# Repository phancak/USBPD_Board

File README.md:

# ⚡ Modular Power Distribution & USB-PD System

<div align="center">
  
  <br>
  <em>4-layer PCB diagram.</em>
</div>

### Intelligent Multi-Source Power Management for Mixed-Signal Platforms

## 📑 Quick Access
* [**📂 View Project Schematics (PDF)**](./Schematics/USBPD_Board_Schematics.pdf)

## 📖 Overview
This project is a high-efficiency, multi-input **Power Distribution Board** designed to provide stable, low-noise rails for interchangeable high-performance modules. It serves as the primary power hub for my **24-bit Precision ADC** and **STM32H7S3 System-on-Module** projects.

The system is engineered for maximum field flexibility, allowing a single instrumentation stack to be powered via laboratory bench supplies, USB-C PD sources, or mobile battery packs.

---

## 🛠 Technical Architecture

### 1. Power Entry & Negotiation
The board features a triple-redundant input strategy to support diverse operating environments:
* **USB Power Delivery:** Utilizes an **MCP2221A-I/ST** USB-to-I2C bridge to communicate with PD controllers and negotiate specific voltage profiles.
* **DC Input:** A standard barrel jack for **12V DC** wall converters, ideal for stationary bench-top development.
* **Battery Port:** A dedicated high-current connector for **Lithium-Ion/Polymer battery packs**, enabling untethered mobile data acquisition.

### 2. Digitally Enhanced Conversion
At the core is the **MCP19061-E/RTB**, a Digitally Enhanced Power Analog (DEPA) controller. 
* **Integrated MCU Control:** Combines the performance of an analog peak current mode controller with the flexibility of a microcontroller.
* **Dynamic Regulation:** Enables real-time telemetry and adjustment of output levels to match the requirements of the downstream load.
* **Protection Circuitry:** Hardware-level Under-Voltage Lockout (UVLO), Over-Voltage Protection (OVP), and thermal shutdown.

### 3. Distribution & Filtering
* **4-Way Power Bus:** Features four precision power connectors to distribute clean rails to a stack of interchangeable boards.
* **Noise Mitigation:** Designed with localized LC filtering and optimized PCB return paths to ensure switching noise from the DC-DC stage does not compromise the 120dB SNR performance of connected ADC modules.

---

## 📐 Hardware Specifications

| Feature | Component / Specification |
| :--- | :--- |
| **Main Controller** | Microchip MCP19061 (Integrated MCU + PWM) |
| **USB Interface** | MCP2221A-I/ST (USB-to-I2C/UART Bridge) |
| **Input Range** | Negotiated USB-PD / 12V DC / Battery |
| **Topology** | Synchronous Buck-Boost Converter |
| **Output Ports** | 4x Interconnect Headers |

---

## 🏗 System Integration Philosophy
This board was developed to solve the "Power Bottleneck" in modular hardware design. By decoupling the power stage from the logic and sensing stages, the system achieves:

1.  **High Modularity:** The "Interchangeable Device" architecture allows for swapping analog front-ends or digital processing units without redesigning the power delivery network.
2.  **Field Readiness:** The seamless transition to battery power makes the entire instrumentation stack viable for real-world environmental and oceanographic data collection.
3.  **Stability:** Centralized regulation reduces ground loops and phase coherency issues common in multi-board "nest" wiring.

---

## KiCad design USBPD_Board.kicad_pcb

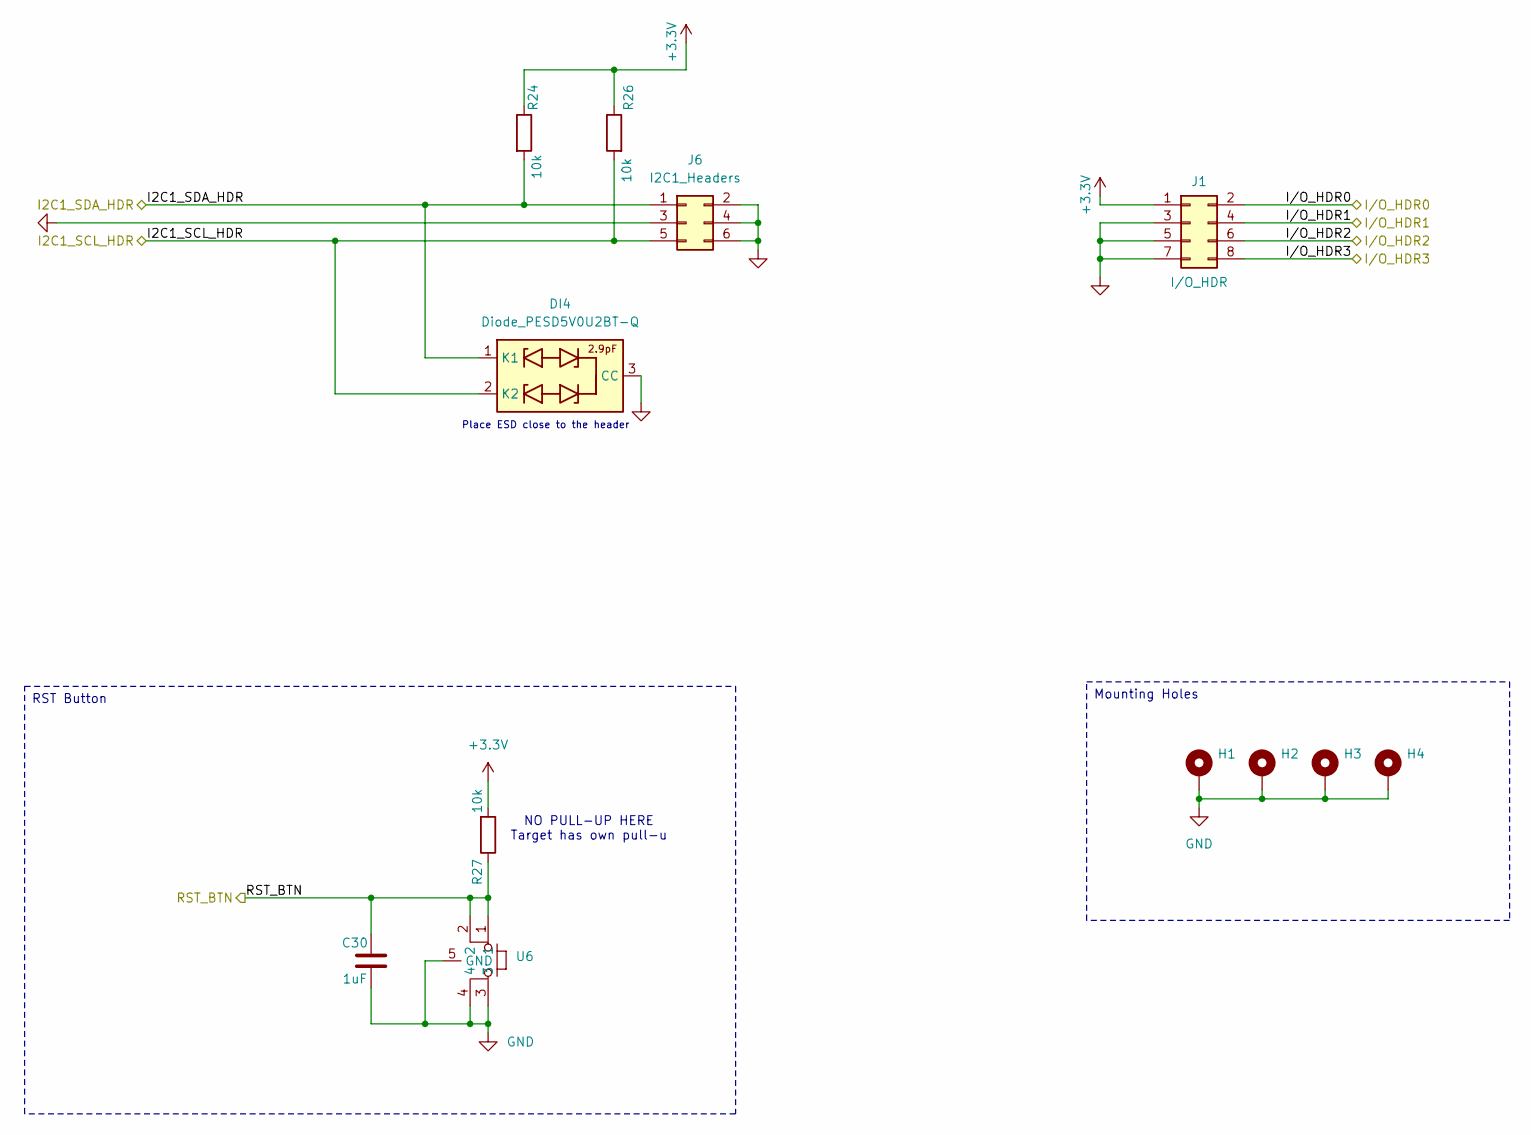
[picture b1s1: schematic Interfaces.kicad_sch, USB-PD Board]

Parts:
C30: 1uF; C_0805_2012Metric
DI4: Diode_PESD5V0U2BT-Q; SOT-23; Manufacturer_Part_Number BZX84C6V2-7-F; Mouser Part Number 621-BZX84C6V2-F
H1, H2, H3, H4: MountingHole_Pad; MountingHole_3.2mm_M3_Pad
J1: I/O_HDR; PinHeader_2x04_P2.54mm_Horizontal
J6: I2C1_Headers; PinHeader_2x03_P2.54mm_Horizontal
R24, R26, R27: 10k; R_0805_2012Metric
U6: Button_KMR231GLFS

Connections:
+3.3V: J1.1, R24.1, R26.1, R27.2; also elsewhere on the board
/Interfaces/I2C1_SCL_HDR: DI4.2 (K2), J6.5, R26.2; also elsewhere on the board
/Interfaces/I2C1_SDA_HDR: DI4.1 (K1), J6.1, R24.2; also elsewhere on the board
/Interfaces/I/O_HDR0: J1.2; also elsewhere on the board
/Interfaces/I/O_HDR1: J1.4; also elsewhere on the board
/Interfaces/I/O_HDR2: J1.6; also elsewhere on the board
/Interfaces/I/O_HDR3: J1.8; also elsewhere on the board
/Interfaces/RST_BTN: C30.2, R27.1, U6.1, U6.2; also elsewhere on the board
GND: C30.1, DI4.3 (CC), H1.1, H2.1, H3.1, H4.1, J1.3, J1.5, J1.7, J6.2, J6.3, J6.4, J6.6, U6.3, U6.4, U6.5 (GND); also elsewhere on the board

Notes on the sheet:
Place ESD close to the header
NO PULL-UP HERE Target has own pull-u
Mounting Holes
RST Button

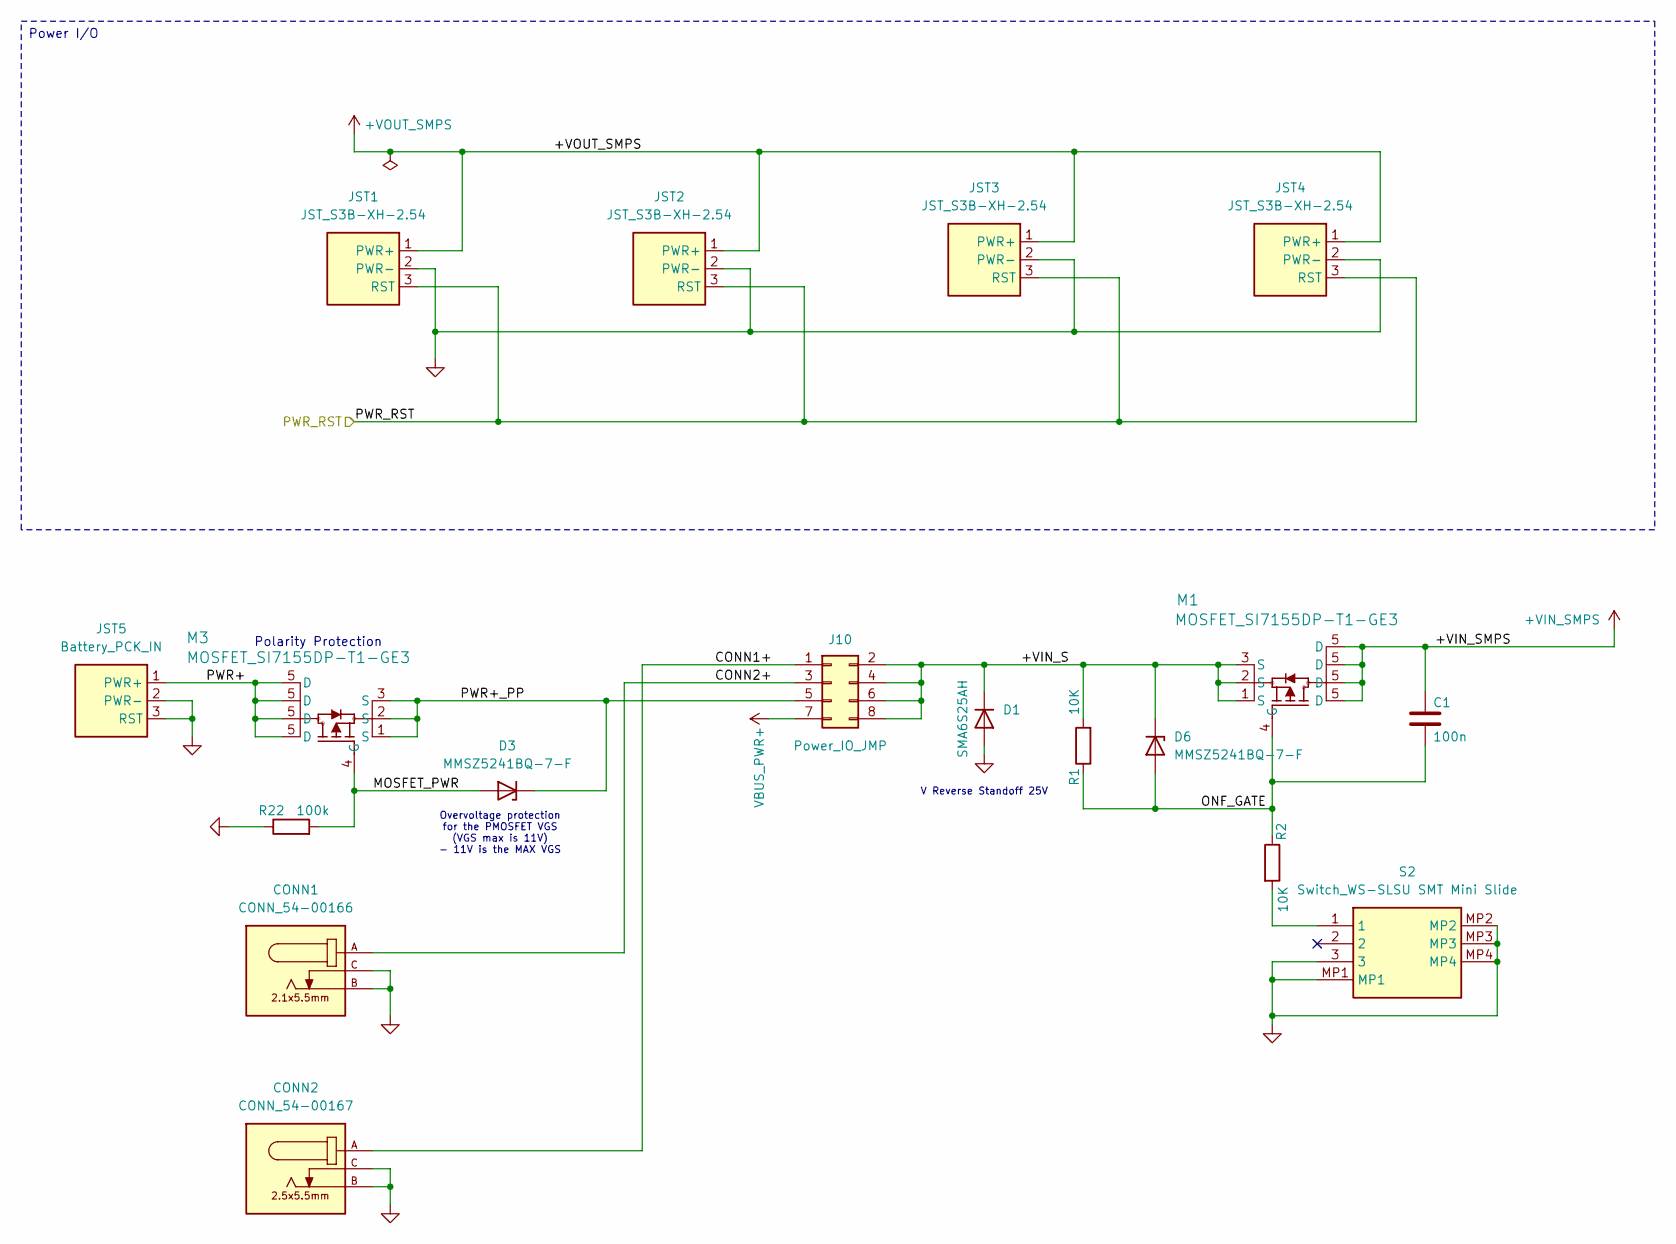
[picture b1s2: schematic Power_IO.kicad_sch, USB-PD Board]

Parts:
C1: 100n; C_0805_2012Metric
CONN1: CONN_54-00166; PARTREV A
CONN2: CONN_54-00167; PARTREV A
D1: SMA6S25AH; D_SOD-123
D3, D6: MMSZ5241BQ-7-F; D_SOD-123
J10: Power_IO_JMP; PinHeader_2x04_P2.54mm_Vertical
JST1, JST2, JST3, JST4: JST_S3B-XH-2.54; JST_S3B-XH-SHDRRA3W64P0X250_1X3_990X1150X610P; Mouser Part Number 306-S3BXHA1LFSN
JST5: Battery_PCK_IN; JST_S3B-XH-SHDRRA3W64P0X250_1X3_990X1150X610P; Mouser Part Number 306-S3BXHA1LFSN
M1, M3: MOSFET_SI7155DP-T1-GE3; MOSFET_SI7155DPT1GE3
R1, R2: 10K; R_0805_2012Metric
R22: 100k; R_0805_2012Metric
S2: Switch_WS-SLSU SMT Mini Slide; Mouser Part Number 710-450404015514

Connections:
+VIN_SMPS: C1.1, M1.5 (D); also elsewhere on the board
+VOUT_SMPS: JST1.1 (PWR+), JST2.1 (PWR+), JST3.1 (PWR+), JST4.1 (PWR+); also elsewhere on the board
/Interfaces/RST_BTN: JST1.3 (RST), JST2.3 (RST), JST3.3 (RST), JST4.3 (RST); also elsewhere on the board
/Power_IO/+VIN_S: D1.1 (K), D6.1 (K), J10.2, J10.4, J10.6, J10.8, M1.1 (S), M1.2 (S), M1.3 (S), R1.2
/Power_IO/CONN1+: CONN2.A, J10.1
/Power_IO/CONN2+: CONN1.A, J10.3
/Power_IO/MOSFET_PWR: D3.2 (A), M3.4 (G), R22.2
/Power_IO/ONF_GATE: C1.2, D6.2 (A), M1.4 (G), R1.1, R2.1
/Power_IO/PWR+: JST5.1 (PWR+), M3.5 (D)
/Power_IO/PWR+_PP: D3.1 (K), J10.5, M3.1 (S), M3.2 (S), M3.3 (S)
GND: CONN1.B, CONN1.C, CONN2.B, CONN2.C, D1.2 (A), JST1.2 (PWR-), JST2.2 (PWR-), JST3.2 (PWR-), JST4.2 (PWR-), JST5.2 (PWR-), JST5.3 (RST), R22.1, S2.3, S2.MP1, S2.MP2, S2.MP3, S2.MP4; also elsewhere on the board
unnamed: R2.2, S2.1
VBUS_PWR+: J10.7; also elsewhere on the board

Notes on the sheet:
Overvoltage protection for the PMOSFET VGS (VGS max is 11V) - 11V is the MAX VGS
V Reverse Standoff 25V
Polarity Protection
Power I/O

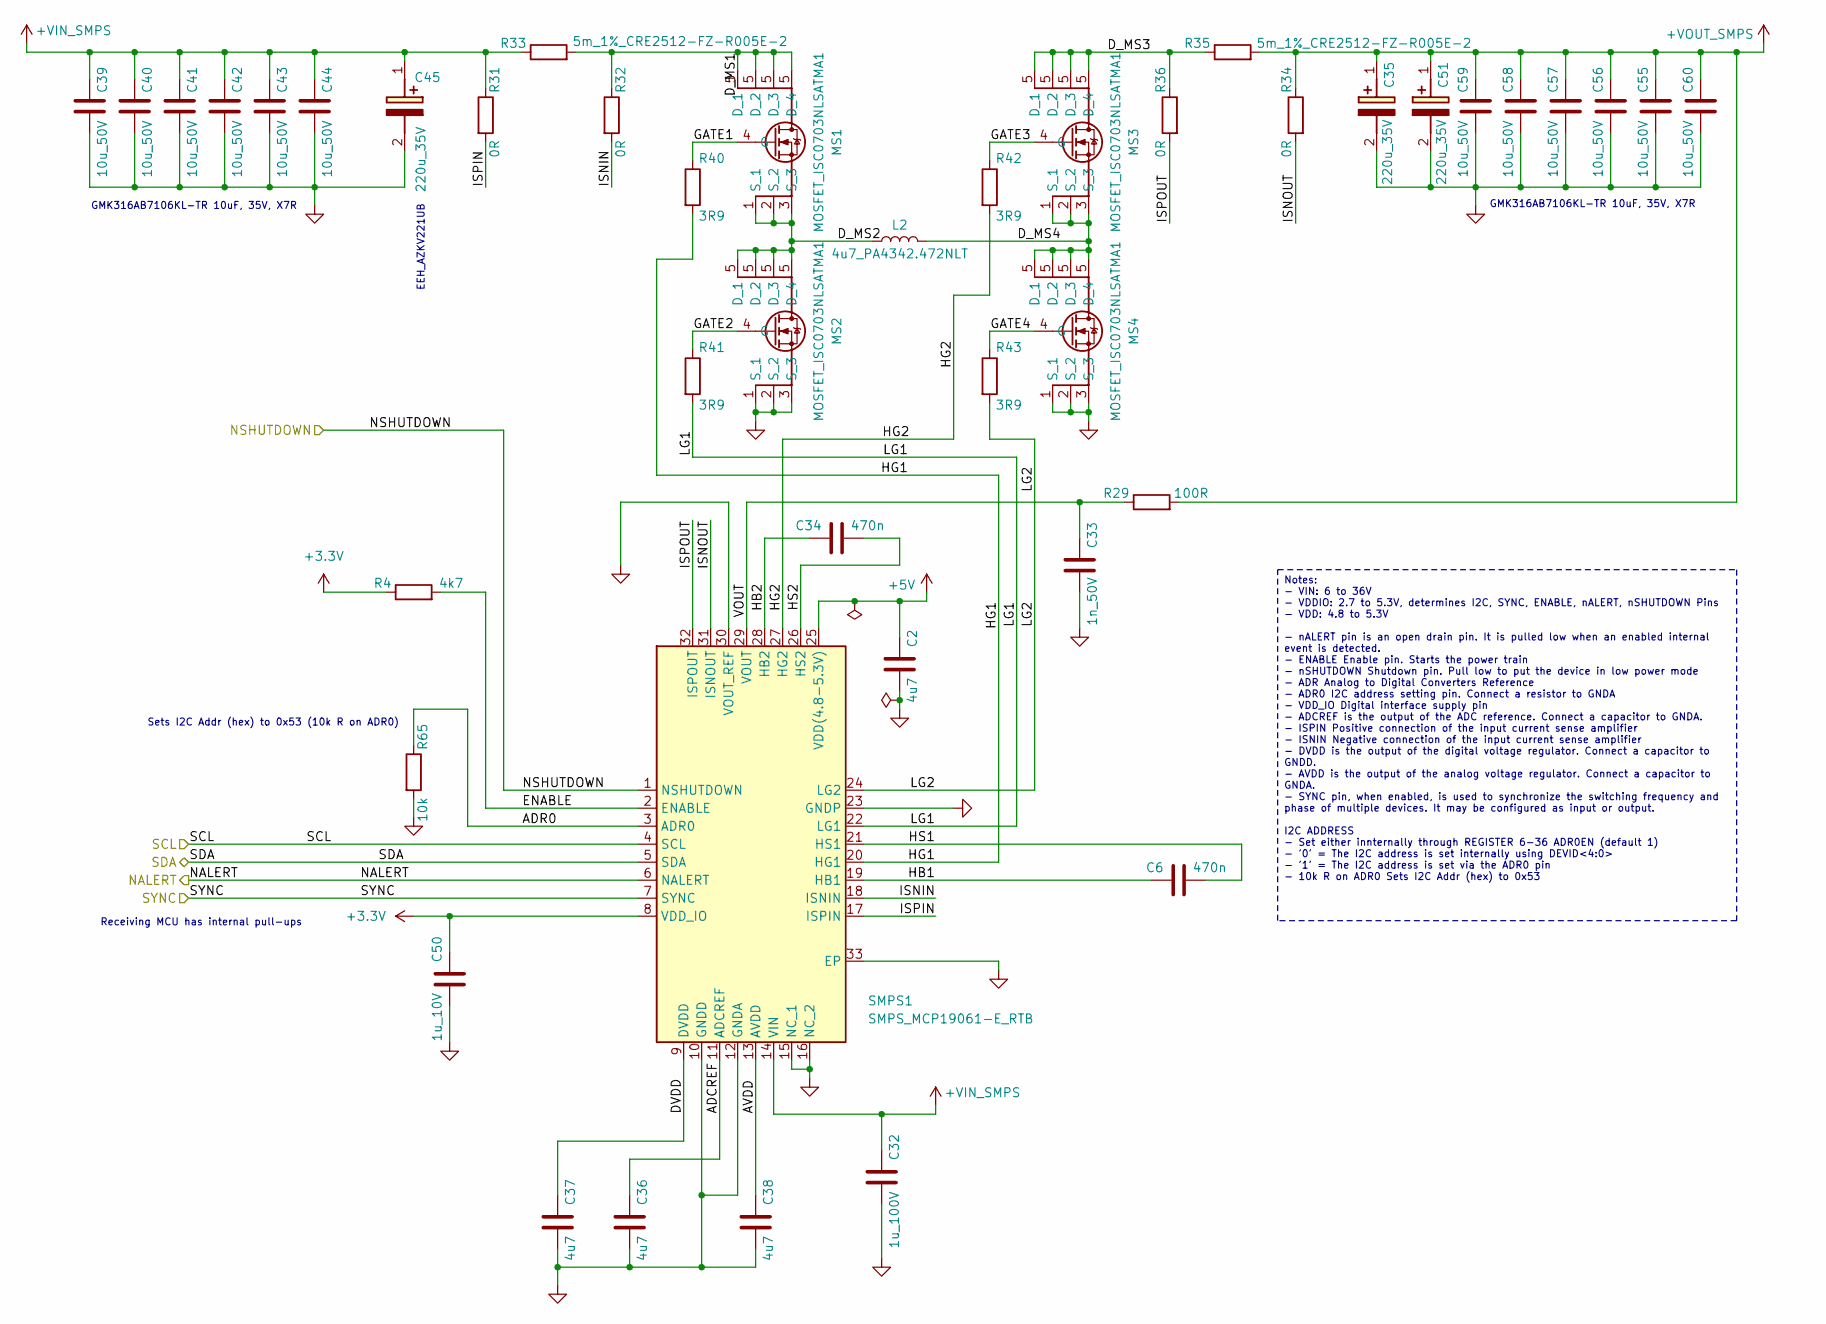
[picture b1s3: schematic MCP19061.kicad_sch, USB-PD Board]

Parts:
C2, C36, C37, C38: 4u7; C_0805_2012Metric
C6, C34: 470n; C_0805_2012Metric
C32: 1u_100V; C_0805_2012Metric
C33: 1n_50V; C_0805_2012Metric
C35, C45, C51: 220u_35V; C_EEHAZKV221UB_CAPPRD350W60D800H950; Mouser Part Number 80-T530Y337M6ATE6
C39, C40, C41, C42, C43, C44, C55, C56, C57, C58, C59, C60: 10u_50V; C_1206_3216Metric
C50: 1u_10V; C_0805_2012Metric
L2: 4u7_PA4342.472NLT; L_PA4342472NLT
MS1, MS2, MS3, MS4: MOSFET_ISC0703NLSATMA1; IPC100N04S51R2ATMA1; Manufacturer_Part_Number IAUCN08S7N034ATMA1
R4: 4k7; R_0805_2012Metric
R29: 100R; R_0805_2012Metric
R31, R32, R34, R36: 0R; R_0805_2012Metric
R33, R35: 5m_1%_CRE2512-FZ-R005E-2; R_2512_6332Metric
R40, R41, R42, R43: 3R9; R_0805_2012Metric
R65: 10k; R_0805_2012Metric
SMPS1: SMPS_MCP19061-E_RTB; SMPS_MCP19061_QFN50P500X500X100-33N-D; Manufacturer_Part_Number MCP19061-E/RTB

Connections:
+3.3V: C50.1, R4.1, SMPS1.8 (VDD_IO); also elsewhere on the board
+5V: C2.1, SMPS1.25 (VDD(4.8-5.3V)); also elsewhere on the board
+VIN_SMPS: C32.1, C39.1, C40.1, C41.1, C42.1, C43.1, C44.1, C45.1 (+), R31.1, R33.1, SMPS1.14 (VIN); also elsewhere on the board
+VOUT_SMPS: C35.1 (+), C51.1 (+), C55.1, C56.1, C57.1, C58.1, C59.1, C60.1, R29.2, R34.1, R35.2; also elsewhere on the board
/Interfaces/I2C1_SCL_HDR: SMPS1.4 (SCL); also elsewhere on the board
/Interfaces/I2C1_SDA_HDR: SMPS1.5 (SDA); also elsewhere on the board
/Interfaces/I/O_HDR0: SMPS1.6 (NALERT); also elsewhere on the board
/Interfaces/I/O_HDR1: SMPS1.7 (SYNC); also elsewhere on the board
/Interfaces/RST_BTN: SMPS1.1 (NSHUTDOWN); also elsewhere on the board
/MCP19061/ADCREF: C36.1, SMPS1.11 (ADCREF)
/MCP19061/ADR0: R65.1, SMPS1.3 (ADR0)
/MCP19061/AVDD: C38.1, SMPS1.13 (AVDD)
/MCP19061/DVDD: C37.1, SMPS1.9 (DVDD)
/MCP19061/D_MS1: MS1.5 (D_1), R32.1, R33.2
/MCP19061/D_MS2: L2.1, MS1.1 (S_1), MS1.2 (S_2), MS1.3 (S_3), MS2.5 (D_1)
/MCP19061/D_MS3: MS3.5 (D_1), R35.1, R36.1
/MCP19061/D_MS4: L2.2, MS3.1 (S_1), MS3.2 (S_2), MS3.3 (S_3), MS4.5 (D_1)
/MCP19061/ENABLE: R4.2, SMPS1.2 (ENABLE)
/MCP19061/GATE1: MS1.4 (G), R40.1
/MCP19061/GATE2: MS2.4 (G), R41.1
/MCP19061/GATE3: MS3.4 (G), R42.1
/MCP19061/GATE4: MS4.4 (G), R43.1
/MCP19061/HB1: C6.1, SMPS1.19 (HB1)
/MCP19061/HB2: C34.1, SMPS1.28 (HB2)
/MCP19061/HG1: R40.2, SMPS1.20 (HG1)
/MCP19061/HG2: R42.2, SMPS1.27 (HG2)
/MCP19061/HS1: C6.2, SMPS1.21 (HS1)
/MCP19061/HS2: C34.2, SMPS1.26 (HS2)
/MCP19061/ISNIN: R32.2, SMPS1.18 (ISNIN)
/MCP19061/ISNOUT: R34.2, SMPS1.31 (ISNOUT)
/MCP19061/ISPIN: R31.2, SMPS1.17 (ISPIN)
/MCP19061/ISPOUT: R36.2, SMPS1.32 (ISPOUT)
/MCP19061/LG1: R41.2, SMPS1.22 (LG1)
/MCP19061/LG2: R43.2, SMPS1.24 (LG2)
/MCP19061/VOUT: C33.1, R29.1, SMPS1.29 (VOUT)
GND: C2.2, C32.2, C33.2, C35.2 (-), C36.2, C37.2, C38.2, C39.2, C40.2, C41.2, C42.2, C43.2, C44.2, C45.2 (-), C50.2, C51.2 (-), C55.2, C56.2, C57.2, C58.2, C59.2, C60.2, MS2.1 (S_1), MS2.2 (S_2), MS2.3 (S_3), MS4.1 (S_1), MS4.2 (S_2), MS4.3 (S_3), R65.2, SMPS1.10 (GNDD), SMPS1.12 (GNDA), SMPS1.15 (NC_1), SMPS1.16 (NC_2), SMPS1.23 (GNDP), SMPS1.30 (VOUT_REF), SMPS1.33 (EP); also elsewhere on the board

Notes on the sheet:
Notes: - VIN: 6 to 36V - VDDIO: 2.7 to 5.3V, determines I2C, SYNC, ENABLE, nALERT, nSHUTDOWN Pins - VDD: 4.8 to 5.3V - nALERT pin is an open drain pin. It is pulled low when an enabled internal event is detected. - ENABLE Enable pin. Starts the power train - nSHUTDOWN Shutdown pin. Pull low to put 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
GMK316AB7106KL-TR 10uF, 35V, X7R
Sets I2C Addr (hex) to 0x53 (10k R on ADR0)
EEH_AZKV221UB
Receiving MCU has internal pull-ups

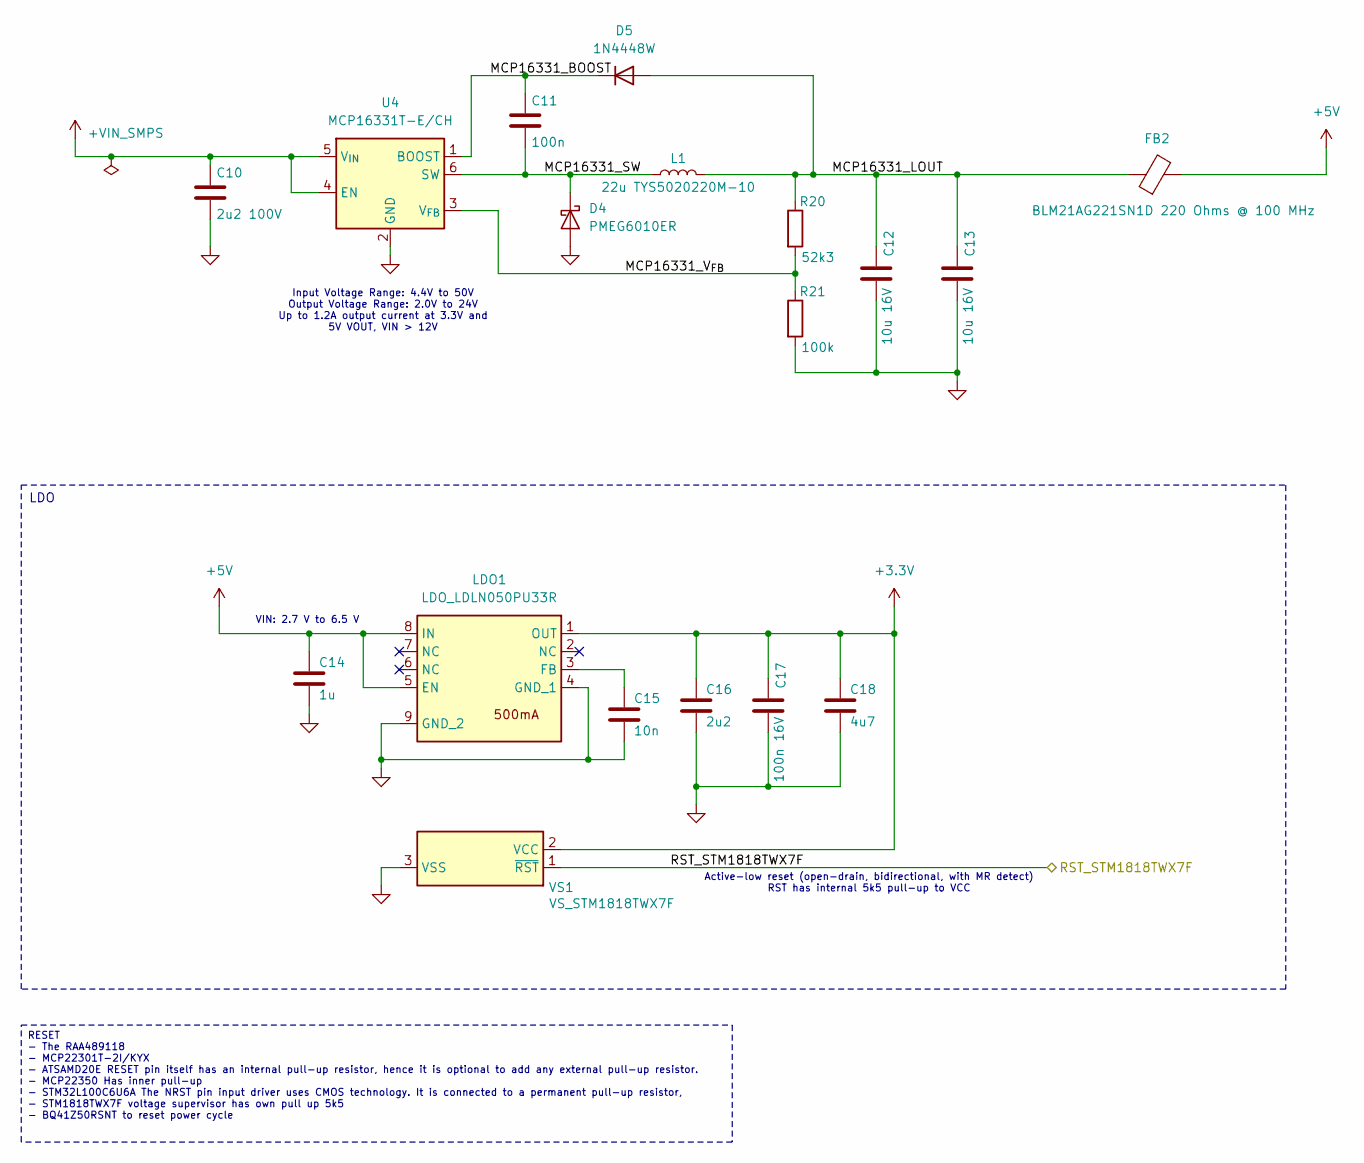
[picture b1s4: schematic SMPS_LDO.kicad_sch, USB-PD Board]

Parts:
C10: 2u2 100V; C_0805_2012Metric
C11: 100n; C_0805_2012Metric
C12, C13: 10u 16V; C_0805_2012Metric
C14: 1u; C_0805_2012Metric
C15: 10n; C_0805_2012Metric
C16: 2u2; C_0805_2012Metric
C17: 100n 16V; C_0805_2012Metric
C18: 4u7; C_0805_2012Metric
D4: PMEG6010ER; Nexperia_CFP3_SOD-123W
D5: 1N4448W; D_SOD-123
FB2: BLM21AG221SN1D 220 Ohms @ 100 MHz; C_0805_2012Metric
L1: 22u TYS5020220M-10; L_Changjiang_FNR5020S
LDO1: LDO_LDLN050PU33R; DFN-8-1EP_3x3mm_P0.65mm_EP1.7x2.05mm; Manufacturer_Part_Number LD39200DPUR; Mouser Part Number 511-LD39200DPUR
R20: 52k3; R_1206_3216Metric
R21: 100k; R_1206_3216Metric
U4: MCP16331T-E/CH; SOT-23-6
VS1: VS_STM1818TWX7F; SOT-23-3_SOT103P237X112-3N; Mouser Part Number 511-STM1813LWX7F

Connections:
+3.3V: C16.1, C17.1, C18.1, LDO1.1 (OUT), VS1.2 (VCC); also elsewhere on the board
+5V: C14.1, FB2.2, LDO1.5 (EN), LDO1.8 (IN); also elsewhere on the board
+VIN_SMPS: C10.1, U4.4 (EN), U4.5 (V_{IN}); also elsewhere on the board
/Interfaces/RST_BTN: VS1.1 (~RST); also elsewhere on the board
/SMPS_LDO/MCP16331_BOOST: C11.1, D5.1 (K), U4.1 (BOOST)
/SMPS_LDO/MCP16331_LOUT: C12.1, C13.1, D5.2 (A), FB2.1, L1.2, R20.1
/SMPS_LDO/MCP16331_SW: C11.2, D4.1 (K), L1.1, U4.6 (SW)
/SMPS_LDO/MCP16331_V_{FB}: R20.2, R21.1, U4.3 (V_{FB})
GND: C10.2, C12.2, C13.2, C14.2, C15.2, C16.2, C17.2, C18.2, D4.2 (A), LDO1.4 (GND_1), LDO1.9 (GND_2), R21.2, U4.2 (GND), VS1.3 (VSS); also elsewhere on the board
unnamed: C15.1, LDO1.3 (FB)

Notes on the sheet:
LDO
RESET - The RAA489118 - MCP22301T-2I/KYX - ATSAMD20E RESET pin itself has an internal pull-up resistor, hence it is optional to add any external pull-up resistor. - MCP22350 Has inner pull-up - STM32L100C6U6A The NRST pin input driver uses CMOS technology. It is connected to a permanent pull-up res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
Active-low reset (open-drain, bidirectional, with MR detect) RST has internal 5k5 pull-up to VCC
Input Voltage Range: 4.4V to 50V Output Voltage Range: 2.0V to 24V Up to 1.2A output current at 3.3V and 5V VOUT, VIN > 12V
VIN: 2.7 V to 6.5 V

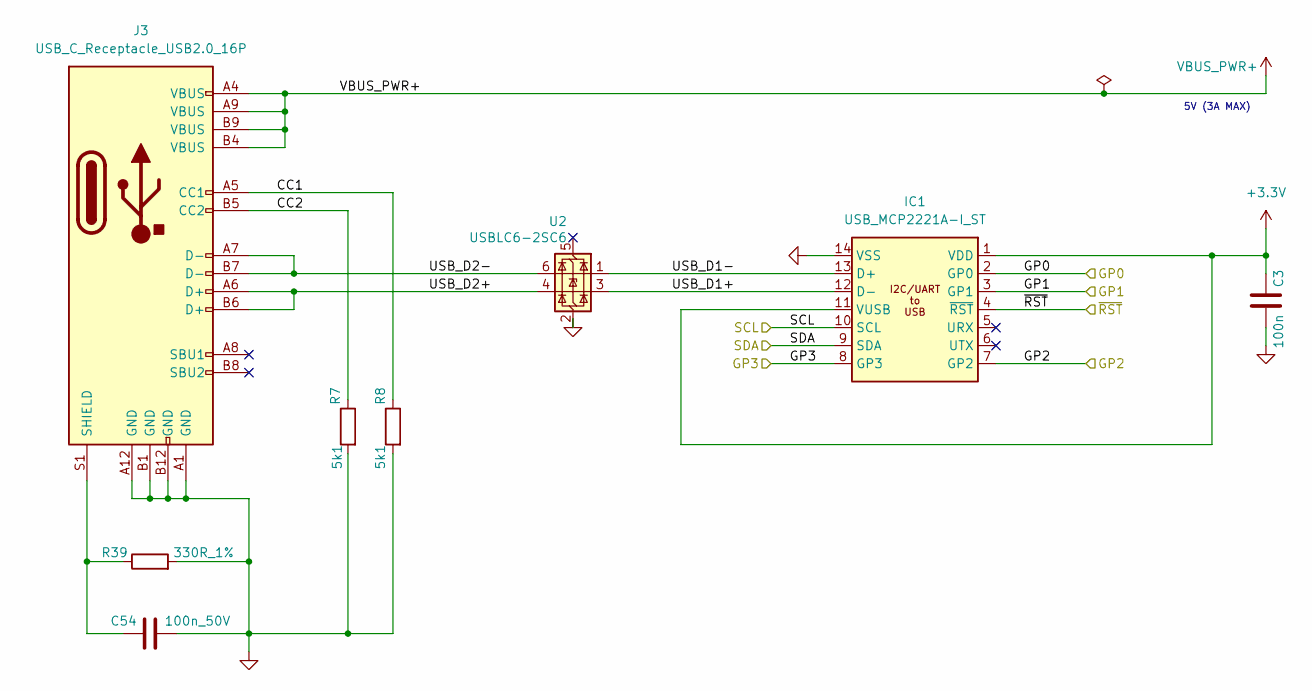
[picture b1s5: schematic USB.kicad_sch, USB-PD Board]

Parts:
C3: 100n; C_0805_2012Metric
C54: 100n_50V; C_0805_2012Metric
IC1: USB_MCP2221A-I_ST; SOP65P640X120-14N; Mouser Part Number 579-MCP2221A-I/ST
J3: USB_C_Receptacle_USB2.0_16P; USB_C_Receptacle_HRO_TYPE-C-31-M-12
R7, R8: 5k1; R_0805_2012Metric
R39: 330R_1%; R_0805_2012Metric
U2: USBLC6-2SC6; SOT-23-6

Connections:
+3.3V: C3.1, IC1.1 (VDD), IC1.11 (VUSB); also elsewhere on the board
/Interfaces/I2C1_SCL_HDR: IC1.10 (SCL); also elsewhere on the board
/Interfaces/I2C1_SDA_HDR: IC1.9 (SDA); also elsewhere on the board
/Interfaces/I/O_HDR2: IC1.2 (GP0); also elsewhere on the board
/Interfaces/I/O_HDR3: IC1.3 (GP1); also elsewhere on the board
/Interfaces/RST_BTN: IC1.4 (~RST); also elsewhere on the board
/USB/CC1: J3.A5 (CC1), R8.1
/USB/CC2: J3.B5 (CC2), R7.1
/USB/GP2: IC1.7 (GP2)
/USB/GP3: IC1.8 (GP3)
/USB/USB_D1+: IC1.12 (D-), U2.3 (I/O2)
/USB/USB_D1-: IC1.13 (D+), U2.1 (I/O1)
/USB/USB_D2+: J3.A6 (D+), J3.B6 (D+), U2.4 (I/O2)
/USB/USB_D2-: J3.A7 (D-), J3.B7 (D-), U2.6 (I/O1)
GND: C3.2, C54.2, IC1.14 (VSS), J3.A1 (GND), J3.A12 (GND), J3.B1 (GND), J3.B12 (GND), R7.2, R8.2, R39.2, U2.2 (GND); also elsewhere on the board
unnamed: C54.1, J3.S1 (SHIELD), R39.1
VBUS_PWR+: J3.A4 (VBUS), J3.A9 (VBUS), J3.B4 (VBUS), J3.B9 (VBUS); also elsewhere on the board

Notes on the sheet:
5V (3A MAX)

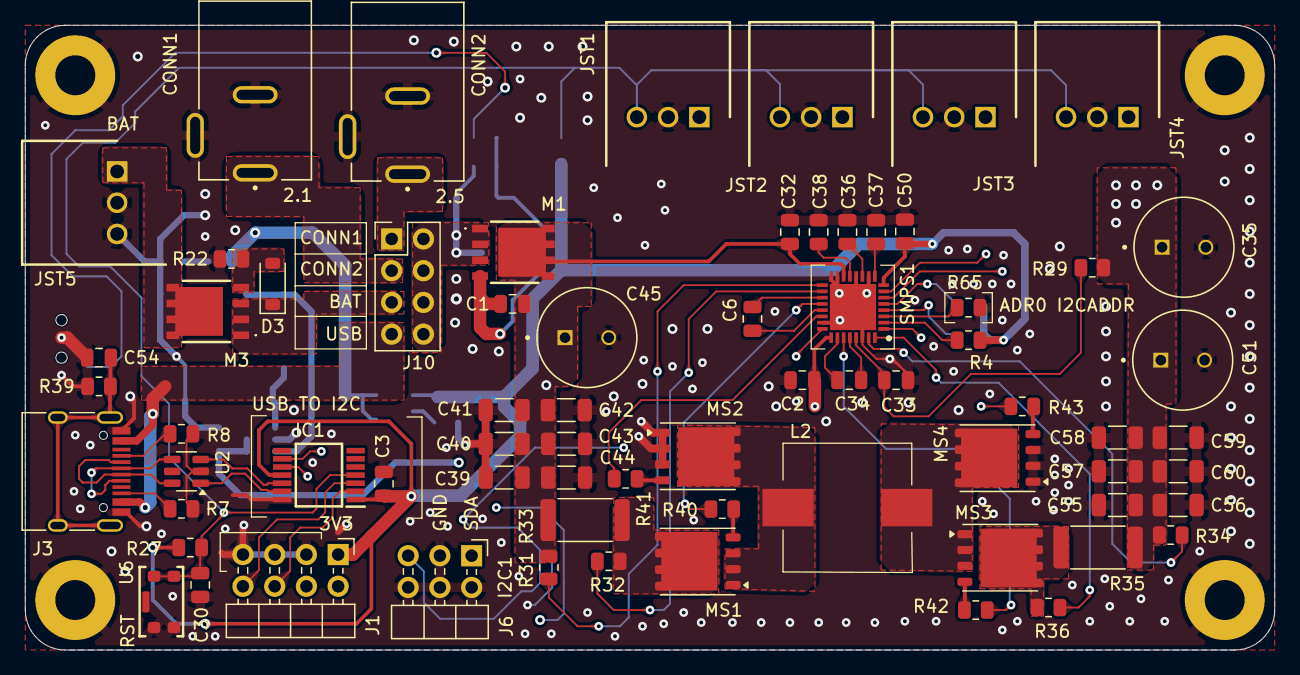
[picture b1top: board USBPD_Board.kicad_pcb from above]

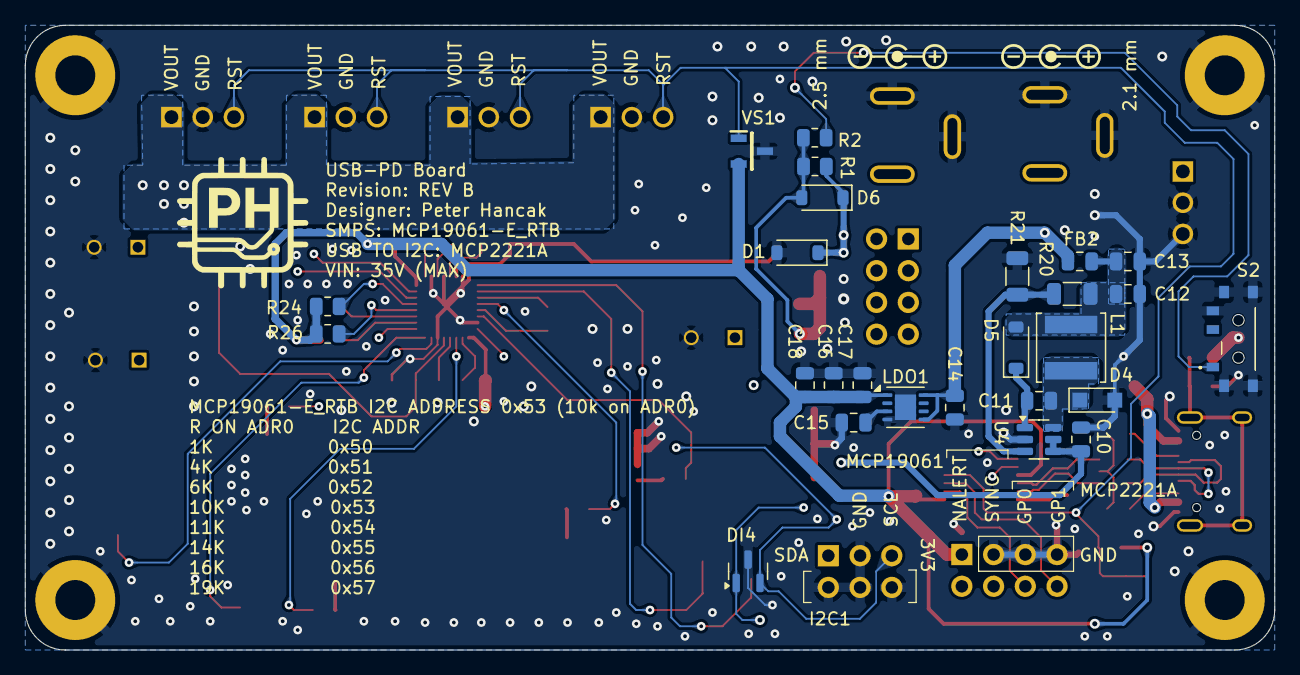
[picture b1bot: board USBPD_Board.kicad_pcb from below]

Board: 4 copper layers, 100.0 x 50.0 mm, 99 parts (26 on the bottom side), 59 nets.

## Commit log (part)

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2026-03-16 Update Readme file
2026-03-25 Updated the Schematics Doc
2026-03-25 Updated Schematics PDF Doc
2026-06-24 Change Kicad version
